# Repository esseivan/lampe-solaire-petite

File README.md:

# Lampe Solaire (version petite)

## Schematic

## 3D

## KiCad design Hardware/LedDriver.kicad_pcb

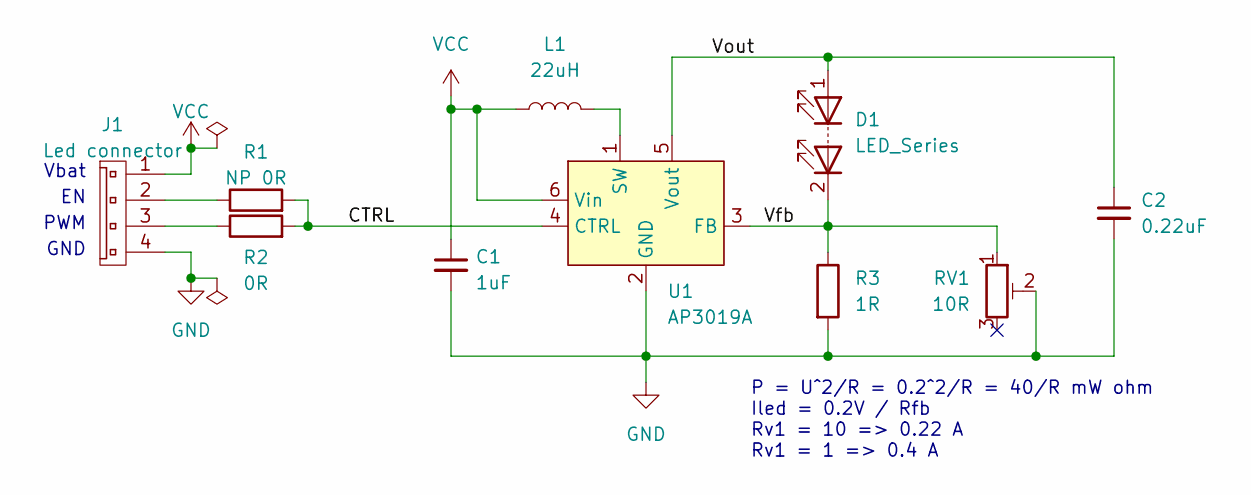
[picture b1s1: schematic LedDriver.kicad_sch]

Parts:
C1: 1uF; C_0805_2012Metric_Pad1.18x1.45mm_HandSolder
C2: 0.22uF; C_0805_2012Metric_Pad1.18x1.45mm_HandSolder
D1: LED_Series; Wire_2x2
J1: Led connector; Connector_4p_m
L1: 22uH; sumida_CDRH_inductor
R1: NP 0R; R_0805_2012Metric_Pad1.20x1.40mm_HandSolder
R2: 0R; R_0805_2012Metric_Pad1.20x1.40mm_HandSolder
R3: 1R; R_0805_2012Metric_Pad1.20x1.40mm_HandSolder
RV1: 10R; Bourns_3362p_trimpot
U1: AP3019A; TSOT-23-6_HandSoldering

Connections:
/CTRL: R1.2, R2.2, U1.4 (CTRL)
/Vfb: D1.2 (K), R3.1, RV1.1, U1.3 (FB)
/Vout: C2.1, D1.1 (A), U1.5 (Vout)
GND: C1.2, C2.2, J1.4, R3.2, RV1.2, U1.2 (GND)
unnamed: J1.2, R1.1
unnamed: J1.3, R2.1
unnamed: L1.2, U1.1 (SW)
VCC: C1.1, J1.1, L1.1, U1.6 (Vin)

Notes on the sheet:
GND
PWM
Vbat
P = U^2/R = 0.2^2/R = 40/R mW ohm Iled = 0.2V / Rfb Rv1 = 10 => 0.22 A Rv1 = 1 => 0.4 A

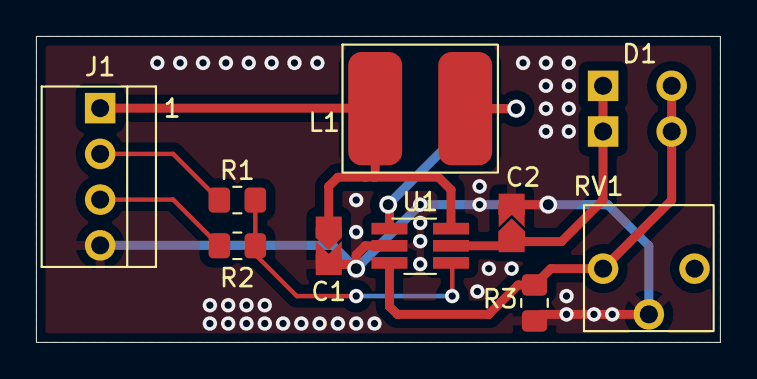
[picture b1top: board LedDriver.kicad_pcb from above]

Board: 2 copper layers, 38.0 x 17.0 mm, 10 parts (0 on the bottom side), 8 nets.

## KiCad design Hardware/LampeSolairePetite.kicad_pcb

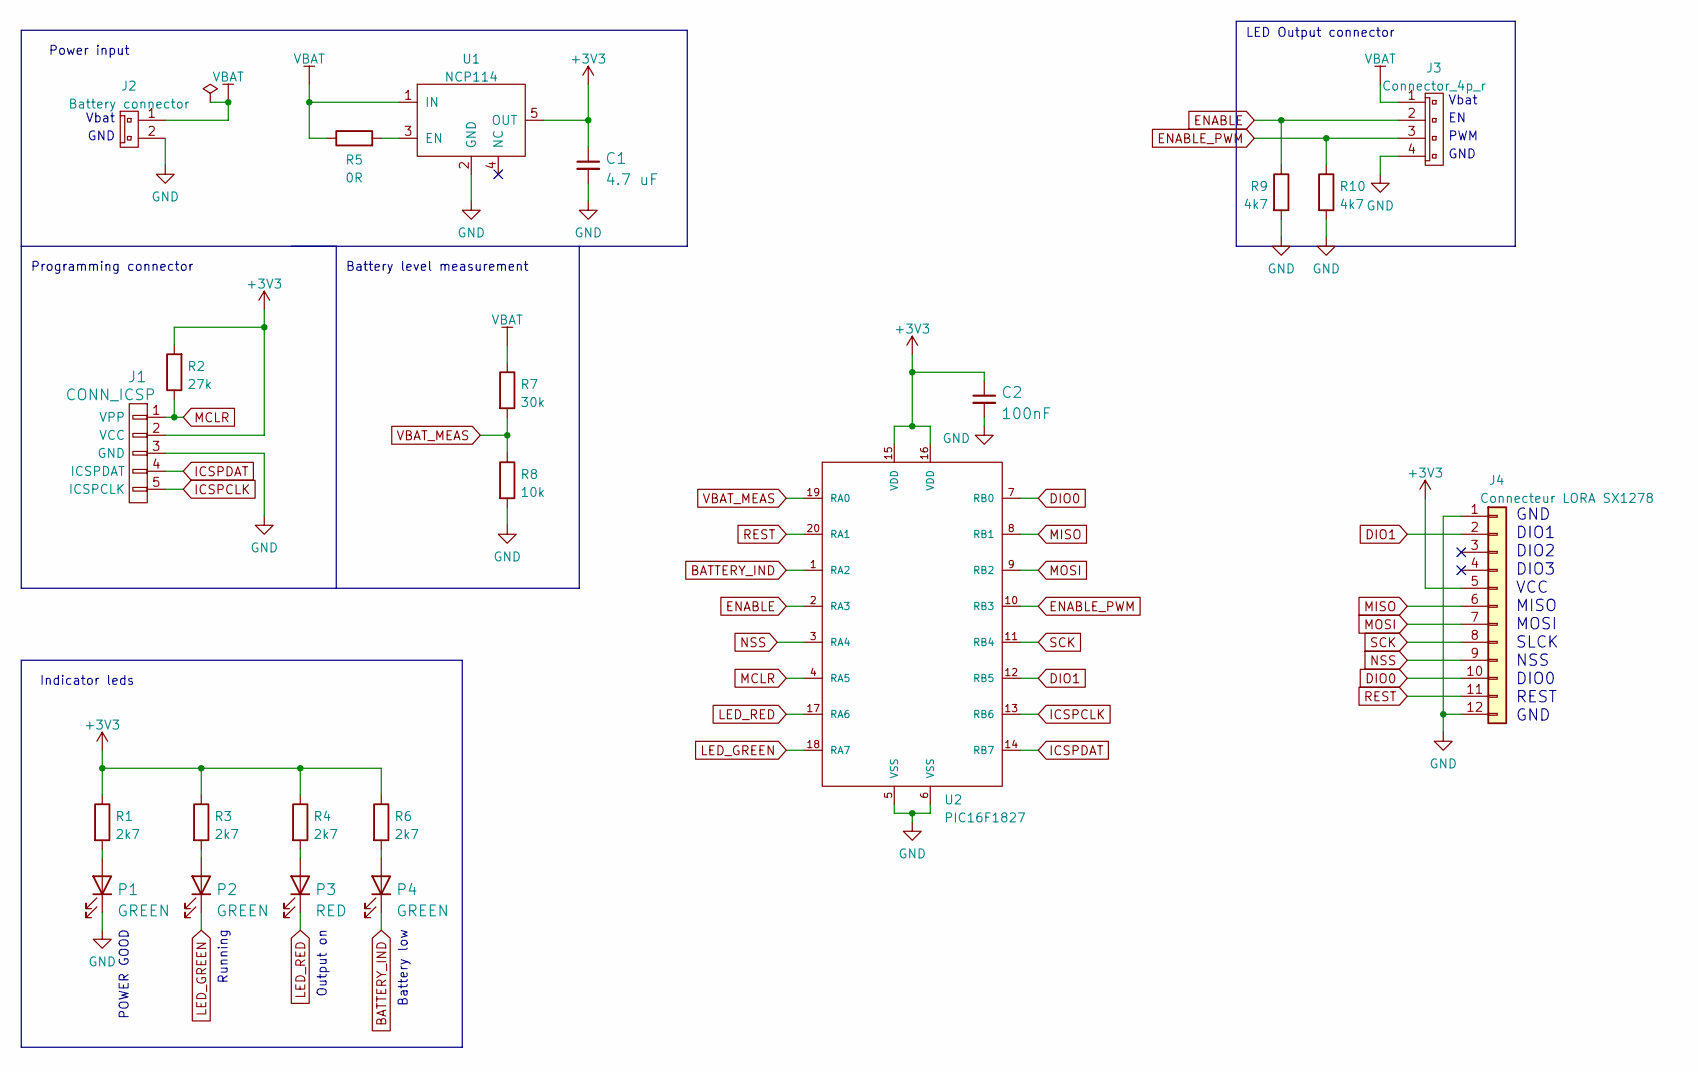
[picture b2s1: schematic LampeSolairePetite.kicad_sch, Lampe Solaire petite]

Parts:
C1: 4.7 uF; C_0805_2012Metric_Pad1.18x1.45mm_HandSolder
C2: 100nF; C_0805_2012Metric_Pad1.18x1.45mm_HandSolder
J1: CONN_ICSP; PinHeader_1x05_P2.54mm_Vertical
J2: Battery connector; Connector_2p_m
J3: Connector_4p_r; Connector_4p_m
J4: Connecteur LORA SX1278; PinHeader_1x12_P1.27mm_Vertical
P1, P2, P4: GREEN; D_0603_1608Metric_Pad1.05x0.95mm_HandSolder
P3: RED; D_0603_1608Metric_Pad1.05x0.95mm_HandSolder
R1, R3, R4, R6: 2k7; R_0805_2012Metric_Pad1.20x1.40mm_HandSolder
R2: 27k; R_0805_2012Metric_Pad1.20x1.40mm_HandSolder
R5: 0R; R_0805_2012Metric_Pad1.20x1.40mm_HandSolder
R7: 30k; R_0805_2012Metric_Pad1.20x1.40mm_HandSolder
R8: 10k; R_0805_2012Metric_Pad1.20x1.40mm_HandSolder
R9, R10: 4k7; R_0805_2012Metric_Pad1.20x1.40mm_HandSolder
U1: NCP114; SOT-23-5_HandSoldering
U2: PIC16F1827; SSOP-20_5.3x7.2mm_P0.65mm

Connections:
+3V3: C1.1, C2.1, J1.2 (VCC), J4.5, R1.1, R2.2, R3.1, R4.1, R6.1, U1.5 (OUT), U2.15 (VDD), U2.16 (VDD)
BATTERY_IND: P4.2 (K), U2.1 (RA2)
DIO0: J4.10, U2.7 (RB0)
DIO1: J4.2, U2.12 (RB5)
ENABLE: J3.2, R9.1, U2.2 (RA3)
ENABLE_PWM: J3.3, R10.1, U2.10 (RB3)
GND: C1.2, C2.2, J1.3 (GND), J2.2, J3.4, J4.1, J4.12, P1.2 (K), R8.2, R9.2, R10.2, U1.2 (GND), U2.5 (VSS), U2.6 (VSS)
ICSPCLK: J1.5 (ICSPCLK), U2.13 (RB6)
ICSPDAT: J1.4 (ICSPDAT), U2.14 (RB7)
LED_GREEN: P2.2 (K), U2.18 (RA7)
LED_RED: P3.2 (K), U2.17 (RA6)
MCLR: J1.1 (VPP), R2.1, U2.4 (RA5)
MISO: J4.6, U2.8 (RB1)
MOSI: J4.7, U2.9 (RB2)
NSS: J4.9, U2.3 (RA4)
unnamed: P1.1 (A), R1.2
unnamed: P2.1 (A), R3.2
unnamed: P3.1 (A), R4.2
unnamed: R5.2, U1.3 (EN)
unnamed: P4.1 (A), R6.2
REST: J4.11, U2.20 (RA1)
SCK: J4.8, U2.11 (RB4)
VBAT: J2.1, J3.1, R5.1, R7.1, U1.1 (IN)
VBAT_MEAS: R7.2, R8.1, U2.19 (RA0)

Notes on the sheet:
POWER GOOD
Vbat
Output on
Power input
PWM
GND
GND DIO1 DIO2 DIO3 VCC MISO MOSI SLCK NSS DIO0 REST GND
Battery low
Battery level measurement
Programming connector
LED Output connector
Indicator leds
Running

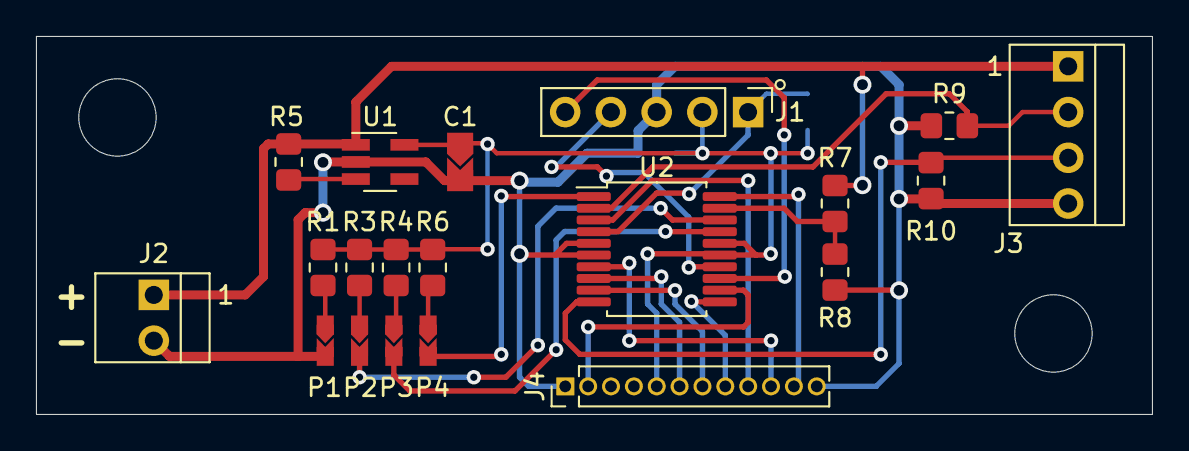
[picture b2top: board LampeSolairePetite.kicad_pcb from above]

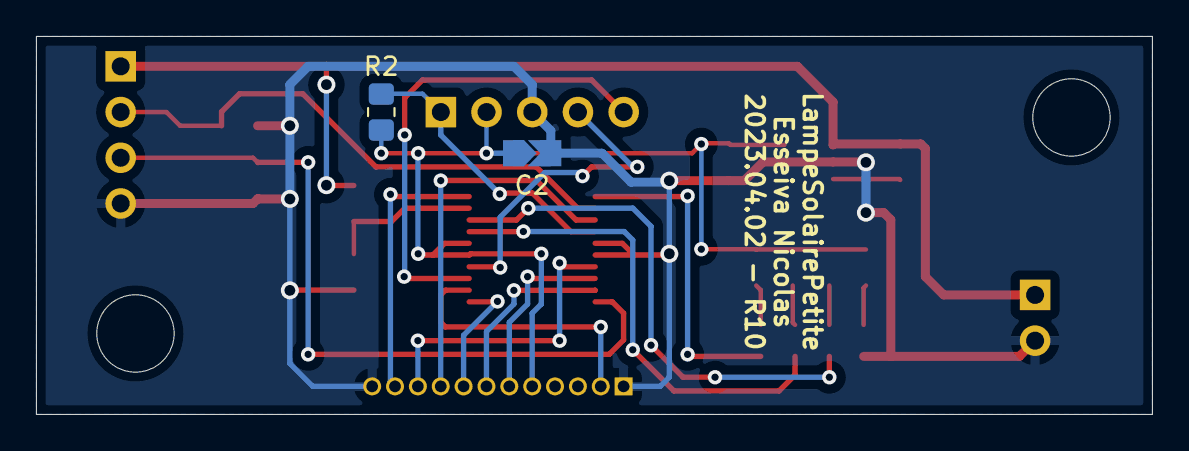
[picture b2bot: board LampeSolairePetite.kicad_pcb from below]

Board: 2 copper layers, 62.0 x 21.0 mm, 22 parts (2 on the bottom side), 24 nets.

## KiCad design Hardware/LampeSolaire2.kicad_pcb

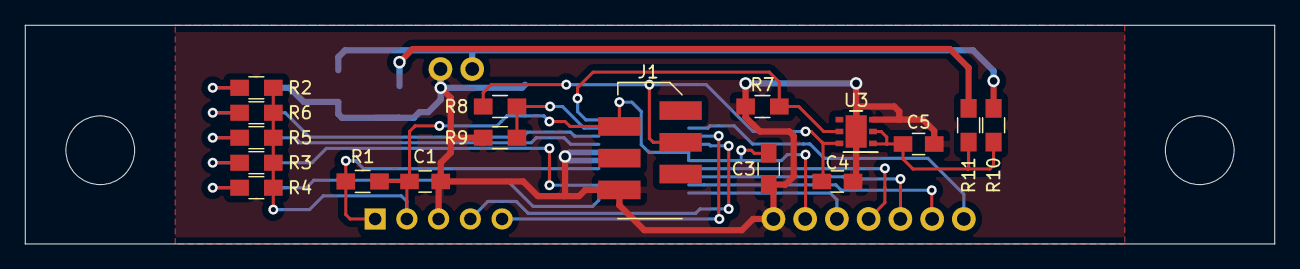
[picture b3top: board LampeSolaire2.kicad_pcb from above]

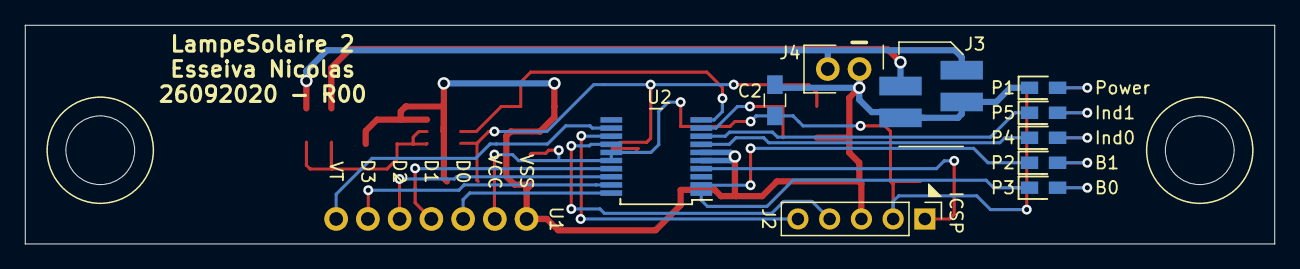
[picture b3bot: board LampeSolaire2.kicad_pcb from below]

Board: 2 copper layers, 100.0 x 17.5 mm, 29 parts (12 on the bottom side), 25 nets.

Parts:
C1, C4, C5: 4.7uF; C_0805_HandSoldering
C2, C3: 100nF; C_0805_HandSoldering
J1: Connector; MicroMatch_6P_Female
J2: CONN_ICSP; Pin_Header_Straight_1x05_Pitch2.54mm
J3: Leds; MicroMatch_4P_Female
J4: Led 2; WireConn_02
P1, P5: GREEN; D_0603_HandSoldering
P2, P3: LED; D_0603_HandSoldering
P4: RED; D_0603_HandSoldering
R1: 27k; R_0805_HandSoldering
R2: 1k5; R_0805_HandSoldering
R3, R5: 330R; R_0805_HandSoldering
R4, R6: 270R; R_0805_HandSoldering
R7: 4k7; R_0805_HandSoldering
R8: 30k; R_0805_HandSoldering
R9: 10k; R_0805_HandSoldering
R10, R11: 10R; R_0805_HandSoldering
U1: RF_RECEIVER
U2: PIC16F1827; SSOP-20_5.3x7.2mm_Pitch0.65mm
U3: LD39200; DFN-6-1EP_3x3mm_Pitch0.95mm
VIS_M3_88mm_space: VIS_M5_88mm

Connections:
/BATTERY_IND_G: P3.1, U2.1
/BATTERY_IND_R: P2.1, U2.2
/BATTERY_LVL: R8.2, R9.1, U2.9
/D0: U1.3, U2.20
/D1: U1.4, U2.17
/D2: U1.5, U2.18
/D3: U1.6, U2.19
/ENABLE: R7.1, U2.10, U3.5
/ICSPCLK: J2.5, U2.13
/ICSPDAT: J2.4, U2.14
/LED_G: P4.1, U2.7
/LED_R: P5.1, U2.8
/VPP: J2.1, R1.2, U2.4
/VT: U1.7, U2.12
GND: C1.2, C2.2, C3.2, C4.2, C5.2, J1.6, J2.3, J3.3, J3.4, J4.2, P1.1, R7.2, R9.2, U1.1, U2.5, U2.6, U3.3, U3.7
unnamed: C5.1, R10.1, R11.1, U3.1, U3.2
unnamed: J3.1, J4.1, R10.2
unnamed: J3.2, R11.2
unnamed: P1.2, R2.2
unnamed: P2.2, R3.2
unnamed: P3.2, R4.2
unnamed: P4.2, R5.2
unnamed: P5.2, R6.2
VBAT: C4.1, J1.3, R8.1, U3.6
VCC_3V3: C1.1, C2.1, C3.1, J1.2, J2.2, R1.1, R2.1, R3.1, R4.1, R5.1, R6.1, U1.2, U2.15, U2.16

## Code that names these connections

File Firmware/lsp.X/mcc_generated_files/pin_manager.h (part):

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// get/set VBAT_MEAS aliases
#define VBAT_MEAS_TRIS                 TRISAbits.TRISA0
#define VBAT_MEAS_LAT                  LATAbits.LATA0
#define VBAT_MEAS_PORT                 PORTAbits.RA0
#define VBAT_MEAS_ANS                  ANSELAbits.ANSA0
#define VBAT_MEAS_SetHigh()            do { LATAbits.LATA0 = 1; } while(0)
#define VBAT_MEAS_SetLow()             do { LATAbits.LATA0 = 0; } while(0)
#define VBAT_MEAS_Toggle()             do { LATAbits.LATA0 = ~LATAbits.LATA0; } while(0)
#define VBAT_MEAS_GetValue()           PORTAbits.RA0
#define VBAT_MEAS_SetDigitalInput()    do { TRISAbits.TRISA0 = 1; } while(0)
#define VBAT_MEAS_SetDigitalOutput()   do { TRISAbits.TRISA0 = 0; } while(0)
#define VBAT_MEAS_SetAnalogMode()      do { ANSELAbits.ANSA0 = 1; } while(0)
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// get/set REST aliases
#define REST_TRIS                 TRISAbits.TRISA1
#define REST_LAT                  LATAbits.LATA1
#define REST_PORT                 PORTAbits.RA1
#define REST_ANS                  ANSELAbits.ANSA1
#define REST_SetHigh()            do { LATAbits.LATA1 = 1; } while(0)
#define REST_SetLow()             do { LATAbits.LATA1 = 0; } while(0)
#define REST_Toggle()             do { LATAbits.LATA1 = ~LATAbits.LATA1; } while(0)
#define REST_GetValue()           PORTAbits.RA1
#define REST_SetDigitalInput()    do { TRISAbits.TRISA1 = 1; } while(0)
#define REST_SetDigitalOutput()   do { TRISAbits.TRISA1 = 0; } while(0)
#define REST_SetAnalogMode()      do { ANSELAbits.ANSA1 = 1; } while(0)
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// get/set BATTERY_IND aliases
#define BATTERY_IND_TRIS                 TRISAbits.TRISA2
#define BATTERY_IND_LAT                  LATAbits.LATA2
#define BATTERY_IND_PORT                 PORTAbits.RA2
#define BATTERY_IND_ANS                  ANSELAbits.ANSA2
#define BATTERY_IND_SetHigh()            do { LATAbits.LATA2 = 1; } while(0)
#define BATTERY_IND_SetLow()             do { LATAbits.LATA2 = 0; } while(0)
#define BATTERY_IND_Toggle()             do { LATAbits.LATA2 = ~LATAbits.LATA2; } while(0)
#define BATTERY_IND_GetValue()           PORTAbits.RA2
#define BATTERY_IND_SetDigitalInput()    do { TRISAbits.TRISA2 = 1; } while(0)
#define BATTERY_IND_SetDigitalOutput()   do { TRISAbits.TRISA2 = 0; } while(0)
#define BATTERY_IND_SetAnalogMode()      do { ANSELAbits.ANSA2 = 1; } while(0)
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// get/set ENABLE aliases
#define ENABLE_TRIS                 TRISAbits.TRISA3
#define ENABLE_LAT                  LATAbits.LATA3
#define ENABLE_PORT                 PORTAbits.RA3
#define ENABLE_ANS                  ANSELAbits.ANSA3
#define ENABLE_SetHigh()            do { LATAbits.LATA3 = 1; } while(0)
#define ENABLE_SetLow()             do { LATAbits.LATA3 = 0; } while(0)
#define ENABLE_Toggle()             do { LATAbits.LATA3 = ~LATAbits.LATA3; } while(0)
#define ENABLE_GetValue()           PORTAbits.RA3
#define ENABLE_SetDigitalInput()    do { TRISAbits.TRISA3 = 1; } while(0)
#define ENABLE_SetDigitalOutput()   do { TRISAbits.TRISA3 = 0; } while(0)
#define ENABLE_SetAnalogMode()      do { ANSELAbits.ANSA3 = 1; } while(0)
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// get/set NSS aliases
#define NSS_TRIS                 TRISAbits.TRISA4
#define NSS_LAT                  LATAbits.LATA4
#define NSS_PORT                 PORTAbits.RA4
#define NSS_ANS                  ANSELAbits.ANSA4
#define NSS_SetHigh()            do { LATAbits.LATA4 = 1; } while(0)
#define NSS_SetLow()             do { LATAbits.LATA4 = 0; } while(0)
#define NSS_Toggle()             do { LATAbits.LATA4 = ~LATAbits.LATA4; } while(0)
#define NSS_GetValue()           PORTAbits.RA4
#define NSS_SetDigitalInput()    do { TRISAbits.TRISA4 = 1; } while(0)
#define NSS_SetDigitalOutput()   do { TRISAbits.TRISA4 = 0; } while(0)
#define NSS_SetAnalogMode()      do { ANSELAbits.ANSA4 = 1; } while(0)
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// get/set LED_RED aliases
#define LED_RED_TRIS                 TRISAbits.TRISA6
#define LED_RED_LAT                  LATAbits.LATA6
#define LED_RED_PORT                 PORTAbits.RA6
#define LED_RED_SetHigh()            do { LATAbits.LATA6 = 1; } while(0)
#define LED_RED_SetLow()             do { LATAbits.LATA6 = 0; } while(0)
#define LED_RED_Toggle()             do { LATAbits.LATA6 = ~LATAbits.LATA6; } while(0)
#define LED_RED_GetValue()           PORTAbits.RA6
#define LED_RED_SetDigitalInput()    do { TRISAbits.TRISA6 = 1; } while(0)
#define LED_RED_SetDigitalOutput()   do { TRISAbits.TRISA6 = 0; } while(0)

// get/set LED_GREEN aliases
#define LED_GREEN_TRIS                 TRISAbits.TRISA7
#define LED_GREEN_LAT                  LATAbits.LATA7
#define LED_GREEN_PORT                 PORTAbits.RA7
#define LED_GREEN_SetHigh()            do { LATAbits.LATA7 = 1; } while(0)
#define LED_GREEN_SetLow()             do { LATAbits.LATA7 = 0; } while(0)
#define LED_GREEN_Toggle()             do { LATAbits.LATA7 = ~LATAbits.LATA7; } while(0)
#define LED_GREEN_GetValue()           PORTAbits.RA7
#define LED_GREEN_SetDigitalInput()    do { TRISAbits.TRISA7 = 1; } while(0)
#define LED_GREEN_SetDigitalOutput()   do { TRISAbits.TRISA7 = 0; } while(0)

// get/set DIO0 aliases
#define DIO0_TRIS                 TRISBbits.TRISB0
#define DIO0_LAT                  LATBbits.LATB0
#define DIO0_PORT                 PORTBbits.RB0
#define DIO0_WPU                  WPUBbits.WPUB0
#define DIO0_SetHigh()            do { LATBbits.LATB0 = 1; } while(0)
#define DIO0_SetLow()             do { LATBbits.LATB0 = 0; } while(0)
#define DIO0_Toggle()             do { LATBbits.LATB0 = ~LATBbits.LATB0; } while(0)
#define DIO0_GetValue()           PORTBbits.RB0
#define DIO0_SetDigitalInput()    do { TRISBbits.TRISB0 = 1; } while(0)
#define DIO0_SetDigitalOutput()   do { TRISBbits.TRISB0 = 0; } while(0)
#define DIO0_SetPullup()          do { WPUBbits.WPUB0 = 1; } while(0)
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#define RB1_SetHigh()            do { LATBbits.LATB1 = 1; } while(0)
#define RB1_SetLow()             do { LATBbits.LATB1 = 0; } while(0)
#define RB1_Toggle()             do { LATBbits.LATB1 = ~LATBbits.LATB1; } while(0)
#define RB1_GetValue()              PORTBbits.RB1
#define RB1_SetDigitalInput()    do { TRISBbits.TRISB1 = 1; } while(0)
#define RB1_SetDigitalOutput()   do { TRISBbits.TRISB1 = 0; } while(0)
#define RB1_SetPullup()             do { WPUBbits.WPUB1 = 1; } while(0)
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#define RB2_SetHigh()            do { LATBbits.LATB2 = 1; } while(0)
#define RB2_SetLow()             do { LATBbits.LATB2 = 0; } while(0)
#define RB2_Toggle()             do { LATBbits.LATB2 = ~LATBbits.LATB2; } while(0)
#define RB2_GetValue()              PORTBbits.RB2
#define RB2_SetDigitalInput()    do { TRISBbits.TRISB2 = 1; } while(0)
#define RB2_SetDigitalOutput()   do { TRISBbits.TRISB2 = 0; } while(0)
#define RB2_SetPullup()             do { WPUBbits.WPUB2 = 1; } while(0)
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// get/set ENABLE_PWM aliases
#define ENABLE_PWM_TRIS                 TRISBbits.TRISB3
#define ENABLE_PWM_LAT                  LATBbits.LATB3
#define ENABLE_PWM_PORT                 PORTBbits.RB3
#define ENABLE_PWM_WPU                  WPUBbits.WPUB3
#define ENABLE_PWM_ANS                  ANSELBbits.ANSB3
#define ENABLE_PWM_SetHigh()            do { LATBbits.LATB3 = 1; } while(0)
#define ENABLE_PWM_SetLow()             do { LATBbits.LATB3 = 0; } while(0)
#define ENABLE_PWM_Toggle()             do { LATBbits.LATB3 = ~LATBbits.LATB3; } while(0)
#define ENABLE_PWM_GetValue()           PORTBbits.RB3
#define ENABLE_PWM_SetDigitalInput()    do { TRISBbits.TRISB3 = 1; } while(0)
#define ENABLE_PWM_SetDigitalOutput()   do { TRISBbits.TRISB3 = 0; } while(0)
#define ENABLE_PWM_SetPullup()          do { WPUBbits.WPUB3 = 1; } while(0)
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#define RB4_SetHigh()            do { LATBbits.LATB4 = 1; } while(0)
#define RB4_SetLow()             do { LATBbits.LATB4 = 0; } while(0)
#define RB4_Toggle()             do { LATBbits.LATB4 = ~LATBbits.LATB4; } while(0)
#define RB4_GetValue()              PORTBbits.RB4
#define RB4_SetDigitalInput()    do { TRISBbits.TRISB4 = 1; } while(0)
#define RB4_SetDigitalOutput()   do { TRISBbits.TRISB4 = 0; } while(0)
#define RB4_SetPullup()             do { WPUBbits.WPUB4 = 1; } while(0)
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// get/set DIO1 aliases
#define DIO1_TRIS                 TRISBbits.TRISB5
#define DIO1_LAT                  LATBbits.LATB5
#define DIO1_PORT                 PORTBbits.RB5
#define DIO1_WPU                  WPUBbits.WPUB5
#define DIO1_ANS                  ANSELBbits.ANSB5
#define DIO1_SetHigh()            do { LATBbits.LATB5 = 1; } while(0)
#define DIO1_SetLow()             do { LATBbits.LATB5 = 0; } while(0)
#define DIO1_Toggle()             do { LATBbits.LATB5 = ~LATBbits.LATB5; } while(0)
#define DIO1_GetValue()           PORTBbits.RB5
#define DIO1_SetDigitalInput()    do { TRISBbits.TRISB5 = 1; } while(0)
#define DIO1_SetDigitalOutput()   do { TRISBbits.TRISB5 = 0; } while(0)
#define DIO1_SetPullup()          do { WPUBbits.WPUB5 = 1; } while(0)
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
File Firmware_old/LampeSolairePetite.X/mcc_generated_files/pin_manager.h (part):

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// get/set D3 aliases
#define D3_TRIS                 TRISAbits.TRISA0
#define D3_LAT                  LATAbits.LATA0
#define D3_PORT                 PORTAbits.RA0
#define D3_ANS                  ANSELAbits.ANSA0
#define D3_SetHigh()            do { LATAbits.LATA0 = 1; } while(0)
#define D3_SetLow()             do { LATAbits.LATA0 = 0; } while(0)
#define D3_Toggle()             do { LATAbits.LATA0 = ~LATAbits.LATA0; } while(0)
#define D3_GetValue()           PORTAbits.RA0
#define D3_SetDigitalInput()    do { TRISAbits.TRISA0 = 1; } while(0)
#define D3_SetDigitalOutput()   do { TRISAbits.TRISA0 = 0; } while(0)
#define D3_SetAnalogMode()      do { ANSELAbits.ANSA0 = 1; } while(0)
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// get/set D0 aliases
#define D0_TRIS                 TRISAbits.TRISA1
#define D0_LAT                  LATAbits.LATA1
#define D0_PORT                 PORTAbits.RA1
#define D0_ANS                  ANSELAbits.ANSA1
#define D0_SetHigh()            do { LATAbits.LATA1 = 1; } while(0)
#define D0_SetLow()             do { LATAbits.LATA1 = 0; } while(0)
#define D0_Toggle()             do { LATAbits.LATA1 = ~LATAbits.LATA1; } while(0)
#define D0_GetValue()           PORTAbits.RA1
#define D0_SetDigitalInput()    do { TRISAbits.TRISA1 = 1; } while(0)
#define D0_SetDigitalOutput()   do { TRISAbits.TRISA1 = 0; } while(0)
#define D0_SetAnalogMode()      do { ANSELAbits.ANSA1 = 1; } while(0)
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// get/set BAT_IND_G aliases
#define BAT_IND_G_TRIS                 TRISAbits.TRISA2
#define BAT_IND_G_LAT                  LATAbits.LATA2
#define BAT_IND_G_PORT                 PORTAbits.RA2
#define BAT_IND_G_ANS                  ANSELAbits.ANSA2
#define BAT_IND_G_SetHigh()            do { LATAbits.LATA2 = 1; } while(0)
#define BAT_IND_G_SetLow()             do { LATAbits.LATA2 = 0; } while(0)
#define BAT_IND_G_Toggle()             do { LATAbits.LATA2 = ~LATAbits.LATA2; } while(0)
#define BAT_IND_G_GetValue()           PORTAbits.RA2
#define BAT_IND_G_SetDigitalInput()    do { TRISAbits.TRISA2 = 1; } while(0)
#define BAT_IND_G_SetDigitalOutput()   do { TRISAbits.TRISA2 = 0; } while(0)
#define BAT_IND_G_SetAnalogMode()      do { ANSELAbits.ANSA2 = 1; } while(0)
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// get/set BAT_IND_R aliases
#define BAT_IND_R_TRIS                 TRISAbits.TRISA3
#define BAT_IND_R_LAT                  LATAbits.LATA3
#define BAT_IND_R_PORT                 PORTAbits.RA3
#define BAT_IND_R_ANS                  ANSELAbits.ANSA3
#define BAT_IND_R_SetHigh()            do { LATAbits.LATA3 = 1; } while(0)
#define BAT_IND_R_SetLow()             do { LATAbits.LATA3 = 0; } while(0)
#define BAT_IND_R_Toggle()             do { LATAbits.LATA3 = ~LATAbits.LATA3; } while(0)
#define BAT_IND_R_GetValue()           PORTAbits.RA3
#define BAT_IND_R_SetDigitalInput()    do { TRISAbits.TRISA3 = 1; } while(0)
#define BAT_IND_R_SetDigitalOutput()   do { TRISAbits.TRISA3 = 0; } while(0)
#define BAT_IND_R_SetAnalogMode()      do { ANSELAbits.ANSA3 = 1; } while(0)
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// get/set NC_1 aliases
#define NC_1_TRIS                 TRISAbits.TRISA4
#define NC_1_LAT                  LATAbits.LATA4
#define NC_1_PORT                 PORTAbits.RA4
#define NC_1_ANS                  ANSELAbits.ANSA4
#define NC_1_SetHigh()            do { LATAbits.LATA4 = 1; } while(0)
#define NC_1_SetLow()             do { LATAbits.LATA4 = 0; } while(0)
#define NC_1_Toggle()             do { LATAbits.LATA4 = ~LATAbits.LATA4; } while(0)
#define NC_1_GetValue()           PORTAbits.RA4
#define NC_1_SetDigitalInput()    do { TRISAbits.TRISA4 = 1; } while(0)
#define NC_1_SetDigitalOutput()   do { TRISAbits.TRISA4 = 0; } while(0)
#define NC_1_SetAnalogMode()      do { ANSELAbits.ANSA4 = 1; } while(0)
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// get/set D1 aliases
#define D1_TRIS                 TRISAbits.TRISA6
#define D1_LAT                  LATAbits.LATA6
#define D1_PORT                 PORTAbits.RA6
#define D1_SetHigh()            do { LATAbits.LATA6 = 1; } while(0)
#define D1_SetLow()             do { LATAbits.LATA6 = 0; } while(0)
#define D1_Toggle()             do { LATAbits.LATA6 = ~LATAbits.LATA6; } while(0)
#define D1_GetValue()           PORTAbits.RA6
#define D1_SetDigitalInput()    do { TRISAbits.TRISA6 = 1; } while(0)
#define D1_SetDigitalOutput()   do { TRISAbits.TRISA6 = 0; } while(0)

// get/set D2 aliases
#define D2_TRIS                 TRISAbits.TRISA7
#define D2_LAT                  LATAbits.LATA7
#define D2_PORT                 PORTAbits.RA7
#define D2_SetHigh()            do { LATAbits.LATA7 = 1; } while(0)
#define D2_SetLow()             do { LATAbits.LATA7 = 0; } while(0)
#define D2_Toggle()             do { LATAbits.LATA7 = ~LATAbits.LATA7; } while(0)
#define D2_GetValue()           PORTAbits.RA7
#define D2_SetDigitalInput()    do { TRISAbits.TRISA7 = 1; } while(0)
#define D2_SetDigitalOutput()   do { TRISAbits.TRISA7 = 0; } while(0)

// get/set LED_G aliases
#define LED_G_TRIS                 TRISBbits.TRISB0
#define LED_G_LAT                  LATBbits.LATB0
#define LED_G_PORT                 PORTBbits.RB0
#define LED_G_WPU                  WPUBbits.WPUB0
#define LED_G_SetHigh()            do { LATBbits.LATB0 = 1; } while(0)
#define LED_G_SetLow()             do { LATBbits.LATB0 = 0; } while(0)
#define LED_G_Toggle()             do { LATBbits.LATB0 = ~LATBbits.LATB0; } while(0)
#define LED_G_GetValue()           PORTBbits.RB0
#define LED_G_SetDigitalInput()    do { TRISBbits.TRISB0 = 1; } while(0)
#define LED_G_SetDigitalOutput()   do { TRISBbits.TRISB0 = 0; } while(0)
#define LED_G_SetPullup()          do { WPUBbits.WPUB0 = 1; } while(0)
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// get/set LED_R aliases
#define LED_R_TRIS                 TRISBbits.TRISB1
#define LED_R_LAT                  LATBbits.LATB1
#define LED_R_PORT                 PORTBbits.RB1
#define LED_R_WPU                  WPUBbits.WPUB1
#define LED_R_ANS                  ANSELBbits.ANSB1
#define LED_R_SetHigh()            do { LATBbits.LATB1 = 1; } while(0)
#define LED_R_SetLow()             do { LATBbits.LATB1 = 0; } while(0)
#define LED_R_Toggle()             do { LATBbits.LATB1 = ~LATBbits.LATB1; } while(0)
#define LED_R_GetValue()           PORTBbits.RB1
#define LED_R_SetDigitalInput()    do { TRISBbits.TRISB1 = 1; } while(0)
#define LED_R_SetDigitalOutput()   do { TRISBbits.TRISB1 = 0; } while(0)
#define LED_R_SetPullup()          do { WPUBbits.WPUB1 = 1; } while(0)
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// get/set BATTERY_LVL aliases
#define BATTERY_LVL_TRIS                 TRISBbits.TRISB2
#define BATTERY_LVL_LAT                  LATBbits.LATB2
#define BATTERY_LVL_PORT                 PORTBbits.RB2
#define BATTERY_LVL_WPU                  WPUBbits.WPUB2
#define BATTERY_LVL_ANS                  ANSELBbits.ANSB2
#define BATTERY_LVL_SetHigh()            do { LATBbits.LATB2 = 1; } while(0)
#define BATTERY_LVL_SetLow()             do { LATBbits.LATB2 = 0; } while(0)
#define BATTERY_LVL_Toggle()             do { LATBbits.LATB2 = ~LATBbits.LATB2; } while(0)
#define BATTERY_LVL_GetValue()           PORTBbits.RB2
#define BATTERY_LVL_SetDigitalInput()    do { TRISBbits.TRISB2 = 1; } while(0)
#define BATTERY_LVL_SetDigitalOutput()   do { TRISBbits.TRISB2 = 0; } while(0)
#define BATTERY_LVL_SetPullup()          do { WPUBbits.WPUB2 = 1; } while(0)
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// get/set ENABLE aliases
#define ENABLE_TRIS                 TRISBbits.TRISB3
#define ENABLE_LAT                  LATBbits.LATB3
#define ENABLE_PORT                 PORTBbits.RB3
#define ENABLE_WPU                  WPUBbits.WPUB3
#define ENABLE_ANS                  ANSELBbits.ANSB3
#define ENABLE_SetHigh()            do { LATBbits.LATB3 = 1; } while(0)
#define ENABLE_SetLow()             do { LATBbits.LATB3 = 0; } while(0)
#define ENABLE_Toggle()             do { LATBbits.LATB3 = ~LATBbits.LATB3; } while(0)
#define ENABLE_GetValue()           PORTBbits.RB3
#define ENABLE_SetDigitalInput()    do { TRISBbits.TRISB3 = 1; } while(0)
#define ENABLE_SetDigitalOutput()   do { TRISBbits.TRISB3 = 0; } while(0)
#define ENABLE_SetPullup()          do { WPUBbits.WPUB3 = 1; } while(0)
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// get/set NC_2 aliases
#define NC_2_TRIS                 TRISBbits.TRISB4
#define NC_2_LAT                  LATBbits.LATB4
#define NC_2_PORT                 PORTBbits.RB4
#define NC_2_WPU                  WPUBbits.WPUB4
#define NC_2_ANS                  ANSELBbits.ANSB4
#define NC_2_SetHigh()            do { LATBbits.LATB4 = 1; } while(0)
#define NC_2_SetLow()             do { LATBbits.LATB4 = 0; } while(0)
#define NC_2_Toggle()             do { LATBbits.LATB4 = ~LATBbits.LATB4; } while(0)
#define NC_2_GetValue()           PORTBbits.RB4
#define NC_2_SetDigitalInput()    do { TRISBbits.TRISB4 = 1; } while(0)
#define NC_2_SetDigitalOutput()   do { TRISBbits.TRISB4 = 0; } while(0)
#define NC_2_SetPullup()          do { WPUBbits.WPUB4 = 1; } while(0)
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// get/set VT aliases
#define VT_TRIS                 TRISBbits.TRISB5
#define VT_LAT                  LATBbits.LATB5
#define VT_PORT                 PORTBbits.RB5
#define VT_WPU                  WPUBbits.WPUB5
#define VT_ANS                  ANSELBbits.ANSB5
#define VT_SetHigh()            do { LATBbits.LATB5 = 1; } while(0)
#define VT_SetLow()             do { LATBbits.LATB5 = 0; } while(0)
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
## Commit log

2021-03-19 initial commit p2
2023-04-02 Nouvelle version
2023-04-02 Renamed files
2023-04-02 removed old files
2023-04-02 created ledDriver schematic
2023-04-02 PCB done for base card
    Maybe add place for screws
2023-04-02 Added holes
2023-04-02 output files
2023-04-03 pcb led driver
2023-04-07 edited libraries
2023-04-07 Finished lampe
2023-04-07 led driver schematic done
2023-04-07 led driver pcb complete
2023-04-07 added gerber zip files
2023-06-20 schematic update
2023-07-05 ledDriver: added ground plane on top
    + added vias
2023-07-05 new firmware
2023-07-05 adapter gitignore + added code
2023-07-05 TX confirmé fonctionnel. Maintenant à faire RX
2023-07-05 made rx but not enough data memory on MCU...
2023-07-05 added missing functions + reduced max buffer size to 32 instead of 256
2023-07-05 leddriver r01 output files

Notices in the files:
Firmware/lsp.X/mcc_generated_files/pin_manager.h:
(c) 2018 Microchip Technology Inc. and its subsidiaries.
